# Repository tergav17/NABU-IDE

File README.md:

# NABU-IDE
This project aims to add an ATA IDE interface to the NABU computer. It is still very much a work in progress, with much designing, fabrication, and testing ahead of it. At the moment, the initial boards are fabricated but need testing.

## Theory of Operation
The ATA IDE bus contains 2 pages of registers, with 8 16-bit registers on each page. However, not every single one of these registers are actually used. The NABU-IDE maps these registers into a total of 16 8-bit registers. When the NABU-IDE is installed in a system, it will occupy the full 16 byte segment of I/O address space allocated to it by the NABU hardware. The base of this will be `C0`, `D0`, `E0`, or `F0` depending on the slot / daisy chain position. For the sake of simplicity, all I/O addresses will be referred to by their base offset.

The first 12 I/O addresses map to the first 6 ATA IDE registers. This works as you would expect, so accessing register 0 would access the lower 8 bits of the ATA data register, and accessing register 1 would access the upper 8 bits. It should be noted that due to the latching logic, a certain order must be followed when accessing a 16-bit ATA register.

- When reading, the lower byte must be read, THEN the upper byte
- When writing, the upper byte must be written, THEN the lower byte

These addresses map as follows:

| ATA Register # | ATA Register Name | Z80 I/O Addresses Used |
| -------------- | ----------------- | ---------------------- |
| 0              | Data              | 0x00, 0x01 |
| 1              | Error             | 0x02, 0x03 |
| 2              | Sector Count      | 0x04, 0x05 |
| 3              | LBA Low           | 0x06, 0x07 |
| 4              | LBA Mid           | 0x08, 0x09 |
| 5              | LBA High          | 0x0A, 0x0B |

The next 4 registers map to the last remaining ATA registers. With these registers, only the first 8 bits can be accessed. This shouldn't be an issue as they are generally unused.

| Z80 I/O Address | ATA Register Name |
| --------------- | ----------------- |
| 0x0C            | Device |
| 0x0D            | Alt Status / Device Control |
| 0x0E            | Status / Command |
| 0x0F            | Undefined |

This should be all one would need to make use of an ATA IDE device. For those who want further reading, I will drop a link to a good document below:

http://users.utcluj.ro/~baruch/media/siee/labor/ATA-Interface.pdf

## BOM
Here is the BOM to build the initial version of the board. I am not sure is 74HCXX logic where work in this case, as there are some timing dependent logic here. Also, components like the Molex power header are not required if just want to run it directly off of the NABU expansion header.

WARNING: If you are building the board (especially Rev 02) to be used on the daisy chain, special attention needs to be paid to the power connector. The design was originally supposed to use the same cable as the FDC, but there is a mistake which connects both pin 4 and pin 5 to +5V. Pin 5 should either be removed from the connector, or not be connected on the cable. 

| Pin Number | Voltage Level |
| ---------- | ------------- |
| 1          | GND           |
| 2          | GND           |
| 3          | N/C           |
| 4          | +5V           |
| 5          | +5V           |

| Quantity | Component | Footprint | Designator | Comments | 
| -------- | --------- | --------- | ---------- | -------- |
| 2        | 74LS574   | DIP-20    | U6, U7 | |
| 2        | 74LS245   | DIP-20    | U1, U8 |  |
| 2        | 74LS32    | DIP-14    | U2, U5 | |
| 1        | 74LS08    | DIP-14    | U3 | |
| 1        | 74LS04    | DIP-14    | U4 | |
| 8        | 100nf Capacitor | Disc 5x2.5x5mm | C2, C3, C4, C5, C6, C7, C8, C10 | |
| 1        | 1nf Capacitor | Disc 5x2.5x5mm | C1 | |
| 1        | 100uf Capacitor | Radial  5x2mm | C9 | |
| 4        | 10K Resistor | Axial 6.3x2.5x7.62mm | R3, R6, R7, R8 | |
| 2        | 3.3K Resistor | Axial 6.3x2.5x7.62mm | R4, R5 | |
| 1        | 180R Resistor | Axial 6.3x2.5x7.62mm | R2 | |
| 1        | 50R Resistor | Axial 6.3x2.5x7.62mm | R1 | |
| 1        | LED          | 3mm | D1 | | 
| 3        | 1x2 Pin Header | 2.54mm | JP1, JP2, JP3 | Will need associated jumpers for configuration |
| 2        | 1x30 Vertical Pin Header | 2.54mm | J3, J4 | Needed for daisy chain |
| 1        | Molex KK-396 1x5 Vertical | 3.96mm | J5 | Needed for daisy chain |
| 1        | 1x30 Horizontal Pin Header | 2.54mm | J2 | Needed for direct-to-expansion |
| 1        | 2x20 IDC Header Horizontal | 2.54mm | J1 | |

A proper KiCAD generated .csv BOM can be found in the KiCAD directory of this repo.

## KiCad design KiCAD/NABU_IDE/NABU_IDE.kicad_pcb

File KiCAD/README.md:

# NABU-IDE
This project aims to add an ATA IDE interface to the NABU computer. It is still very much a work in progress, with much designing, fabrication, and testing ahead of it.

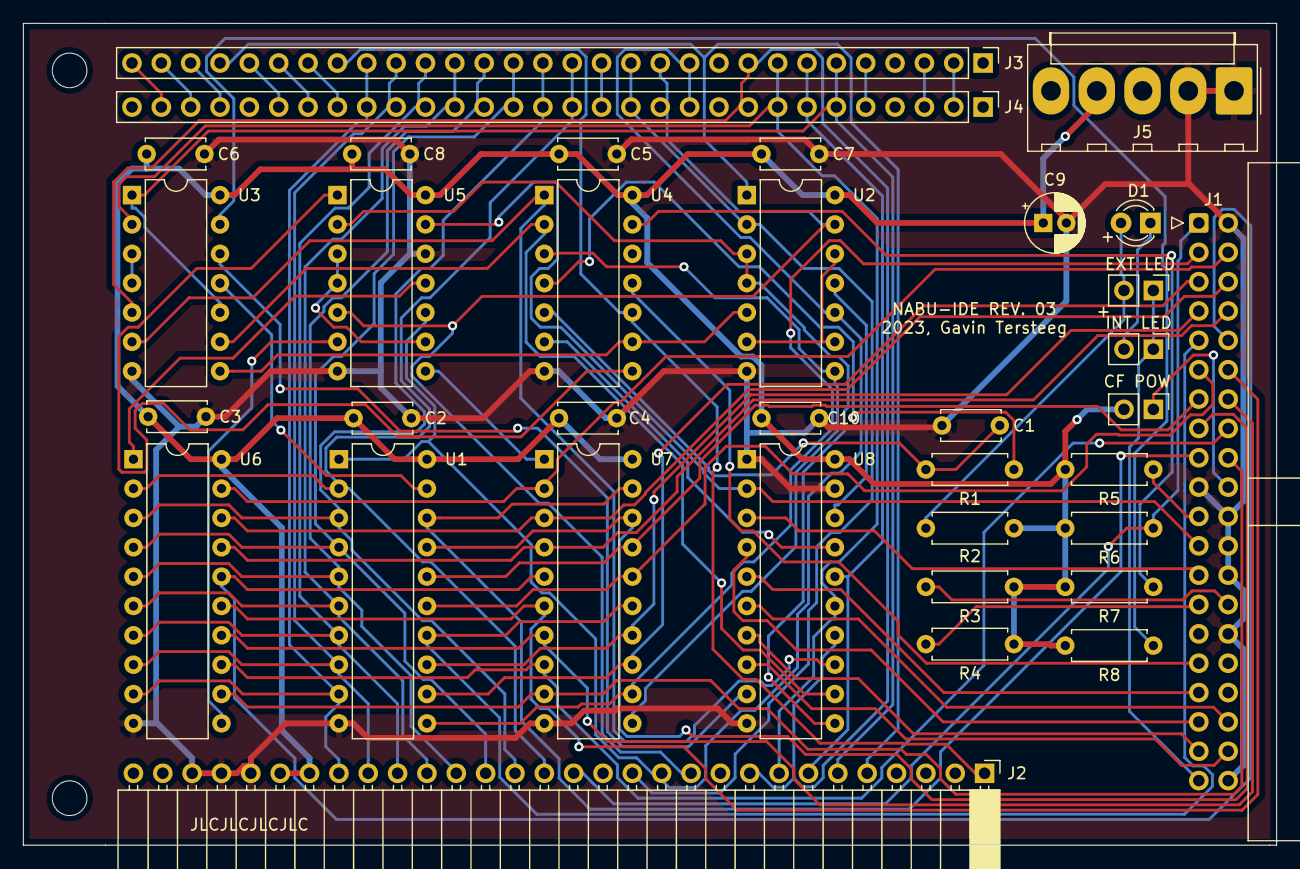
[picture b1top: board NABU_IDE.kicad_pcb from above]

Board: 2 copper layers, 108.5 x 71.1 mm, 37 parts (0 on the bottom side), 81 nets.

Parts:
C1: 1nF; C_Disc_D5.0mm_W2.5mm_P5.00mm
C2, C3, C4, C5, C6, C7, C8, C10: 100nf; C_Disc_D5.0mm_W2.5mm_P5.00mm
C9: 100uf; CP_Radial_D5.0mm_P2.00mm
D1: LED 3mm; LED_D3.0mm
H1, H2: MountingHole; MountingHole_3mm
J1: IDE ATA Bus; IDC-Header_2x20_P2.54mm_Horizontal
J2: NABU Expansion Header; PinSocket_1x30_P2.54mm_Horizontal
J3: NABU Daisy Chain In; PinHeader_1x30_P2.54mm_Vertical
J4: NABU Daisy Chain Out; PinHeader_1x30_P2.54mm_Vertical
J5: NABU External Power; Molex_KK-396_A-41791-0005_1x05_P3.96mm_Vertical
JP1: External LED; PinHeader_1x02_P2.54mm_Vertical
JP2: Internal LED; PinHeader_1x02_P2.54mm_Vertical
JP3: CF Power Option; PinHeader_1x02_P2.54mm_Vertical
R1: 50R; R_Axial_DIN0207_L6.3mm_D2.5mm_P7.62mm_Horizontal
R2: 180R; R_Axial_DIN0207_L6.3mm_D2.5mm_P7.62mm_Horizontal
R3, R6, R7, R8: 10K; R_Axial_DIN0207_L6.3mm_D2.5mm_P7.62mm_Horizontal
R4, R5: 3.3K; R_Axial_DIN0207_L6.3mm_D2.5mm_P7.62mm_Horizontal
U1, U8: 74LS245; DIP-20_W7.62mm
U2, U5: 74LS32; DIP-14_W7.62mm
U3: 74LS08; DIP-14_W7.62mm
U4: 74LS04; DIP-14_W7.62mm
U6, U7: 74LS574; DIP-20_W7.62mm

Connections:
/*IDE_ACTIVE: J1.39, JP1.1, JP2.1
/*IDE_CS0: U3.6, U4.1, U8.13
/*IDE_CS0_BUF: J1.37, U8.7
/*IDE_CS1: U3.9, U4.2, U8.12
/*IDE_CS1_BUF: J1.38, U8.8
/*IDE_RD: U4.6, U8.17
/*IDE_RD_BUF: J1.25, U8.3
/*IDE_WR: U2.11, U8.18
/*IDE_WR_BUF: J1.23, U5.13, U8.2
/*NABU_CS: J2.5, J3.27, U2.1
/*NABU_INT: J2.1, J3.23, U4.10
/*NABU_IORQ: J2.13, J3.13, J4.13, U2.2
/*NABU_RD: J2.12, J3.11, J4.11, U1.1, U2.10, U5.10
/*NABU_RESET: J1.1, J2.15, R6.2
/*NABU_SEL: U2.3, U2.4, U5.2, U8.11
/*NABU_SEL_DLY: U1.19, U3.11
/*NABU_WR: J2.11, J3.12, J4.12, U2.13, U5.5
/+5V: C2.1, C3.1, C4.1, C5.1, C6.1, C7.1, C8.1, C9.1, C10.1, J2.24, J2.25, J5.4, JP3.2, R2.1, R3.1, R4.1, R5.1, R6.1, R7.2, R8.2, U1.20, U2.14, U3.14, U4.14, U5.14, U6.20, U7.20, U8.20
/BUF_D0: J1.17, U1.18, U7.19
/BUF_D1: J1.15, U1.17, U7.18
/BUF_D2: J1.13, U1.16, U7.17
/BUF_D3: J1.11, U1.15, U7.16
/BUF_D4: J1.9, U1.14, U7.15
/BUF_D5: J1.7, U1.13, U7.14
/BUF_D6: J1.5, U1.12, U7.13
/BUF_D7: J1.3, U1.11, U7.12
/CHAIN_3.58Mhz: J3.3, J4.3
/CHAIN_AUDIO: J3.5, J4.5
/CHAIN_CS0: J3.28, J4.27
/CHAIN_CS1: J3.29, J4.28
/CHAIN_CS2: J3.30, J4.29
/CHAIN_INT0: J3.24, J4.23
/CHAIN_INT1: J3.25, J4.24
/CHAIN_INT2: J3.26, J4.25
/CHAIN_INTAK: J3.2, J4.2
/CHAIN_WAIT: J3.14, J4.14
/ENDIAN: U2.5, U3.8, U4.9
/IDE_CFPOWER: J1.20, JP3.1
/IDE_CSEL: J1.28, R3.2
/IDE_D8: J1.4, U6.19, U7.2
/IDE_D9: J1.6, U6.18, U7.3
/IDE_D10: J1.8, U6.17, U7.4
/IDE_D11: J1.10, U6.16, U7.5
/IDE_D12: J1.12, U6.15, U7.6
/IDE_D13: J1.14, U6.14, U7.7
/IDE_D14: J1.16, U6.13, U7.8
/IDE_D15: J1.18, U6.12, U7.9
/IDE_DMARQ: J1.21, R5.2
/IDE_IORDY: J1.27, R4.2
/IDE_IRQ: J1.31, U4.11
/NABU_A0: J2.6, J3.6, J4.6, U3.1, U3.10
/NABU_A1: J2.7, J3.7, J4.7, U8.16
/NABU_A1_BUF: J1.35, U8.4
/NABU_A2: J2.8, J3.8, J4.8, U3.2, U8.15
/NABU_A2_BUF: J1.33, U8.5
/NABU_A3: J2.9, J3.9, J4.9, U3.5, U8.14
/NABU_A3_BUF: J1.36, U8.6
/NABU_D0: J2.16, J3.15, J4.15, U1.2, U6.2
/NABU_D1: J2.17, J3.16, J4.16, U1.3, U6.3
/NABU_D2: J2.18, J3.17, J4.17, U1.4, U6.4
/NABU_D3: J2.19, J3.18, J4.18, U1.5, U6.5
/NABU_D4: J2.20, J3.19, J4.19, U1.6, U6.6
/NABU_D5: J2.21, J3.20, J4.20, U1.7, U6.7
/NABU_D6: J2.22, J3.21, J4.21, U1.8, U6.8
/NABU_D7: J2.23, J3.22, J4.22, U1.9, U6.9
GND: C1.1, C2.2, C3.2, C4.2, C5.2, C6.2, C7.2, C8.2, C9.2, C10.2, J1.2, J1.19, J1.22, J1.24, J1.26, J1.30, J1.40, J2.26, J2.27, J2.28, J5.1, J5.2, U1.10, U2.7, U3.7, U4.7, U5.7, U5.12, U6.10, U7.10, U8.1, U8.10, U8.19
unnamed: C1.2, R1.1, U4.5
unnamed: D1.1, JP2.2
unnamed: D1.2, JP1.2, R2.2
unnamed: R1.2, U4.4
unnamed: R7.1, U4.13
unnamed: R8.1, U3.13
unnamed: U2.8, U4.3, U7.11
unnamed: U2.6, U2.9, U2.12
unnamed: U3.3, U3.4
unnamed: U3.12, U8.9
unnamed: U4.8, U5.1
unnamed: U5.3, U5.4, U5.9
unnamed: U5.6, U6.11
unnamed: U5.8, U7.1
unnamed: U5.11, U6.1

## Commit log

2022-12-31 Changed schematics to allow for daisy chaining
2022-12-31 Pull up resistors and filter caps added
2022-12-31 Started work on new PCB layout
2023-01-01 Finished up most of the initial layout
2023-01-03 Added buffering for address line and signals, also some timing stuff
2023-01-03 Updated PCB, but have not placed components yet
2023-01-04 Finished routing board and added mounting holes
2023-01-10 Added gerbers and made some silkscreen changes
2023-01-11 Updated design a little bit
2023-08-17 Fixed power connector issue and added CF power option
